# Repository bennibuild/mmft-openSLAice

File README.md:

# OpenSLAice

<p align="center">
  <picture>
    
  </picture>
</p>

</div>

OpenSLAice is a specialized slicer for masked sterolithography (mSLA) 3D printing of microfluidic devices. It addresses the unique challenges of printing microfluidic devices with high precision and reliability. It is part of the [Munich Microfluidics Toolkit (MMFT)](https://www.cda.cit.tum.de/research/microfluidics/munich-microfluidics-toolkit/) by the [Chair for Design Automation](https://www.cda.cit.tum.de/) at the Technical University of Munich.

## Overview

1. **Setup:**
   - *Initialization*: Printer (build volume, pixel resolution, z-stage movement) and resin (exposure time with regard to layer thickness) parameters are loaded.
   - *Geometry Import*: The 3D part (STL) is imported and metadata included.

2. **Core Slicing:**
   - *Feature Detection and Orientation*: The microfluidic channel network is detected and the 3D object is auto-oriented and placed accordingly to optimize channel alignment and reduce stair-step artifacts.
   - *Z-Slicing*: Layer heights for slicing are determined and the object is sliced along the z-axis into 2D planes, based on dynamic or static layer heights.
   - *XY-Rasterization*: Each 2D plane is converted into a bitmap mask aligned to the LCD pixel grid.

3. **Output and Calibration:**
   - *(Optional) Automatic Part Arrangement*: If several objects are printed at the same time, they are arranged on the build platform.
   - *Export*: The printer-specific export file including the printer, resin, and layer data is created and exported.
   - *(Optional) Exposure Calibration*: If necessary, the resin–printer combination can be calibrated using a single print evaluation.

## Contributors

OpenSLAice is a specialized slicer for microfluidic SLA/mSLA 3D printing, developed as part of a thesis project by Benjamin Liertz. 

## Getting Started

### Prerequisites

- Python 3.9+
- Jupyter Notebook

### Installation dependencies:

```bash
pip install -r requirements.txt
```

### Usage

#### Main Application

Open the main Jupyter notebook `OpenSLAice.ipynb` to access a simple example for how to use OpenSLAice.

#### Exposure Calibration

A specialized notebook is available for calibrating exposure `exp_calibration.ipynb`.

This notebook determine the needed resin model parameter used in the physical model for exposure time prediction. With these parameters and some metadata you can add any resin to the OpenSLAice database and use it for printing.

## Irradiance Measurements

The currently used resin parameters are where calibrated using the Anycubic Mono 4 Ultra with a measured irradiance of 1938.24 μW/cm² at 400nm at the FEP film. 
To ensure accurate exposure times across different printers, an irradiance sensor is provided to reuse the physical model.

In the `irradiance_sensor` directory, you'll find resources for building and using an irradiance sensor:

- **KiCad PCB Design**: Complete PCB design files for building a sensor board
- **Arduino Code**: Firmware for an ESP32-S3 SuperMinni with OPT3002 irradiance sensor
- **Usage Instructions**: How to measure and calibrate UV irradiance for your printer

This sensor allows precise measurement of your printer's light source intensity, enabling reuse of the physical model for exposure time prediction across different printers without needing to recalibrate.

## Project Structure

```
OpenSLAice/
├── examples/                # Example STL files and projects
│   ├── stls/                # Directory for STL files
│   │   ├── mixer.stl        # Example mixer STL
│   │   └── ELISA_chip.stl   # Example ELISA chip STL
│   └── ...                  # Other example projects
├── irradiance_sensor/       # Resources for irradiance sensor
│   ├── firmware/            # ESP32-S3 firmware for sensor
│   ├── kicad_pcb/           # KiCad PCB design files
│   └── README.md            # Sensor usage instructions
├── OpenSLAice.ipynb         # Main Jupyter notebook for OpenSLAice
├── exp_calibration.ipynb    # Jupyter notebook for exposure calibration
├── requirements.txt         # Python package dependencies
└── README.md                # Project overview and documentation
```

## Licensing

This repository is licensed under the MIT License. However, the following STL files are included under the Creative Commons Attribution 4.0 International License (CC BY 4.0):

- `examples/stls/mixer.stl`
- `examples/stls/ELISA_chip.stl`

See the [ATTRIBUTION.md](ATTRIBUTION.md) file for details.

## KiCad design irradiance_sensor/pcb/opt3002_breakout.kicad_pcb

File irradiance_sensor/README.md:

# OPT3002 Irradiance Sensor for mSLA Printers

<div align="center">
<div style="display:flex; justify-content:center; gap:10px;">

</div>

**A custom UV irradiance measurement solution for resin 3D printer calibration**

</div>

## Overview

This custom irradiance sensor uses the Texas Instruments OPT3002 light sensor coupled with an ESP32-S3 SuperMini microcontroller to provide accurate UV light measurements for mSLA 3D printers.
These measurements are essential for proper exposure calibration across different printers without recalibrating the resin model parameters.

## Sensor Specifications

The OPT3002 sensor features:
- 23-bit effective dynamic range with automatic gain scaling
- Wavelength response from 300nm to 1000nm
- Spectral response at 390-410nm (typical for mSLA printers) is approximately 0.68 relative to the reference wavelength of 505nm
- Wide measurement range from 1.8 nW/cm² to 4 mW/cm²
- I²C interface for communication

## Hardware Design

The custom breakout board is designed specifically for mSLA printer measurement:

- **Front side**: Contains only the sensor and four solder pads (add solder to them to add some defined points of contact)
- **Back side**: Houses the ESP32-S3 SuperMini and i2c breakout, so the sensor can also be used with other microcontrollers
- **Solder spacers**: Ensure the PCB sits flat on the printer screen with the sensor nearly in contact with the FEP film

## Firmware

The Arduino firmware in the `firmware` directory configures the OPT3002 sensor for:

- Automatic range scaling
- 800ms integration time for low-noise measurements
- Continuous conversion mode
- Output rate of 1Hz via serial interface

### ESP32-S3 SuperMini Setup

1. **Prerequisites**:
   - Arduino IDE with ESP32 board support installed
   - [ClosedCube_OPT3002 library](https://github.com/closedcube/ClosedCube_OPT3002_Arduino)

2. **Enable USB CDC on First Upload**:

   Important: Before first upload, hold the BOOT button while connecting the ESP32-S3.

   In Arduino IDE, select Tools > USB CDC On Boot > Enabled

3. **Upload Instructions**:
   - Select `ESP32S3 Supermini` as the board
   - Set USB CDC On Boot: Enabled
   - Press and hold the BOOT button (only needed for the first upload)
   - Connect the ESP32-S3 SuperMini via USB-C
   - Release the BOOT button after connection
   - Upload the sketch from Arduino IDE

## Usage Instructions

1. Place the sensor directly on the printer screen (with the FEP film in place)
2. Connect the ESP32-S3 SuperMini to your computer via USB-C
3. Open Arduino Serial Monitor (9600 baud)
4. The sensor will output readings in μW/cm² at 1Hz
5. Take multiple measurements at different screen positions for accurate calibration

## Measurement Interpretation

The OPT3002 outputs irradiance values in μW/cm², but these need correction for UV wavelengths:

1. Record the measured irradiance value
2. Apply spectral response correction: `Actual Irradiance = Measured Irradiance ÷ 0.68`
3. Use this corrected value as $I_0$ in exposure calculations

For example, a measurement of 1318.0 μW/cm² would translate to an effective $I_0$ of 1938.24 μW/cm² at 400nm.

## Calibration Process

For best results:

1. Take measurements at multiple positions across the print area
2. Record 5-6 readings at each position
3. Calculate the mean irradiance value
4. Apply the spectral correction factor (÷ 0.68)
5. Use this value in the OpenSLAice physical exposure model

## Further Reading

For more information about the physical model and how these measurements are used in exposure calculations, please refer to the main OpenSLAice documentation.

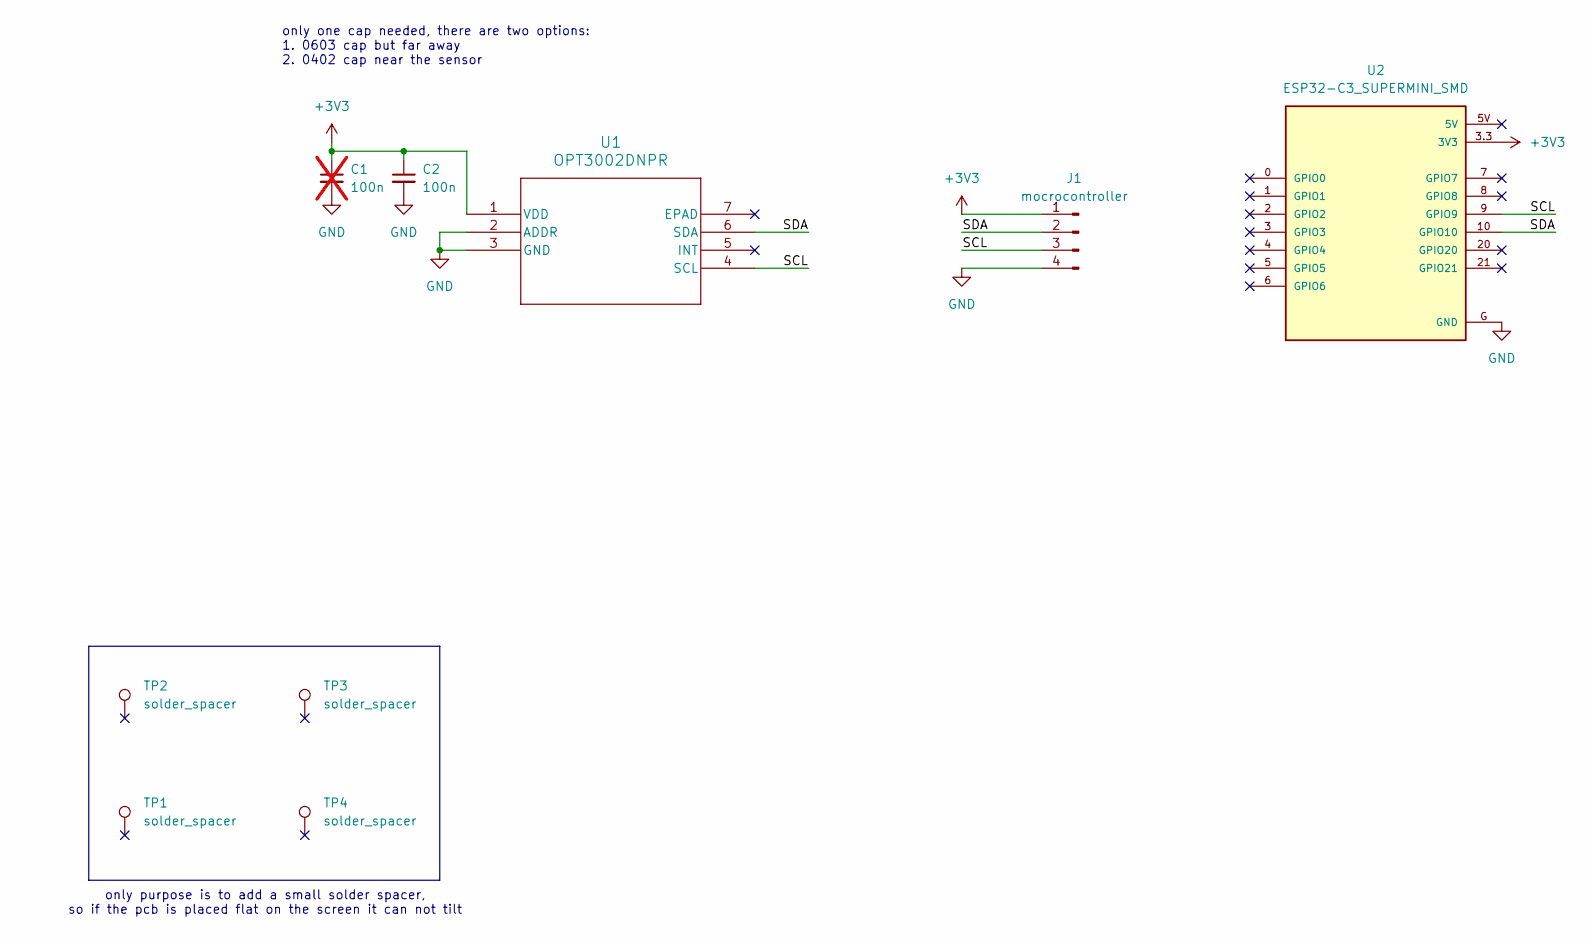
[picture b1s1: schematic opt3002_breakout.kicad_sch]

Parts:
C1: 100n; C_0603_1608Metric; not fitted
C2: 100n; C_0402_1005Metric
J1: mocrocontroller; smd_pads_P2.54mm
TP1, TP2, TP3, TP4: solder_spacer; TestPoint_Pad_D3.0mm
U1: OPT3002DNPR; opt3002
U2: ESP32-C3_SUPERMINI_SMD; MODULE_ESP32-C3_SUPERMINI

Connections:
+3V3: C1.1, C2.1, J1.1, U1.1 (VDD), U2.3.3 (3V3)
/SCL: J1.3, U1.4 (SCL), U2.9 (GPIO9)
/SDA: J1.2, U1.6 (SDA), U2.10 (GPIO10)
GND: C1.2, C2.2, J1.4, U1.2 (ADDR), U1.3 (GND), U2.G (GND)

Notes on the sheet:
only one cap needed, there are two options: 1. 0603 cap but far away 2. 0402 cap near the sensor
only purpose is to add a small solder spacer, so if the pcb is placed flat on the screen it can not tilt

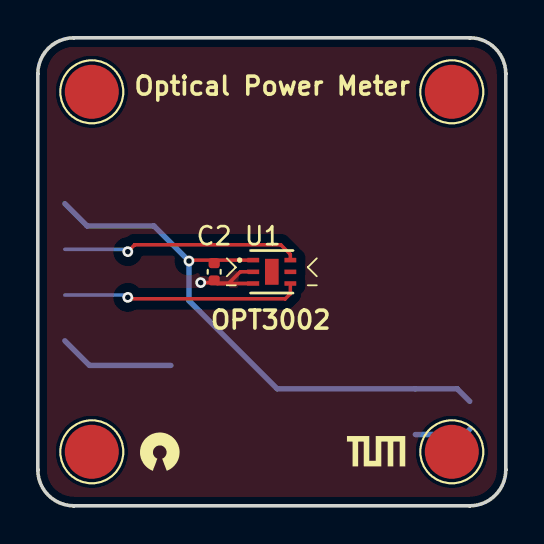
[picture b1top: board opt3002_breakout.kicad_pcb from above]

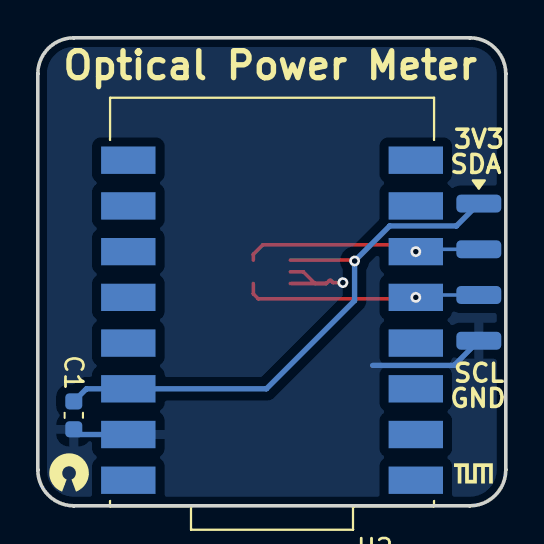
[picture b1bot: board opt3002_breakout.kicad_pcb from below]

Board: 2 copper layers, 26.0 x 26.0 mm, 9 parts (3 on the bottom side), 4 nets.

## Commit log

2025-07-29 initial commit (License)
2025-07-29 copied code from original repo
2025-07-30 Rename spheroid_vsmall.stl to spheroid-trap.stl
2025-10-21 added elegoo mars 5 ultra implementation
2025-10-22 implemented v0 of the .goo file format

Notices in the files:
README.md:
License: MIT
